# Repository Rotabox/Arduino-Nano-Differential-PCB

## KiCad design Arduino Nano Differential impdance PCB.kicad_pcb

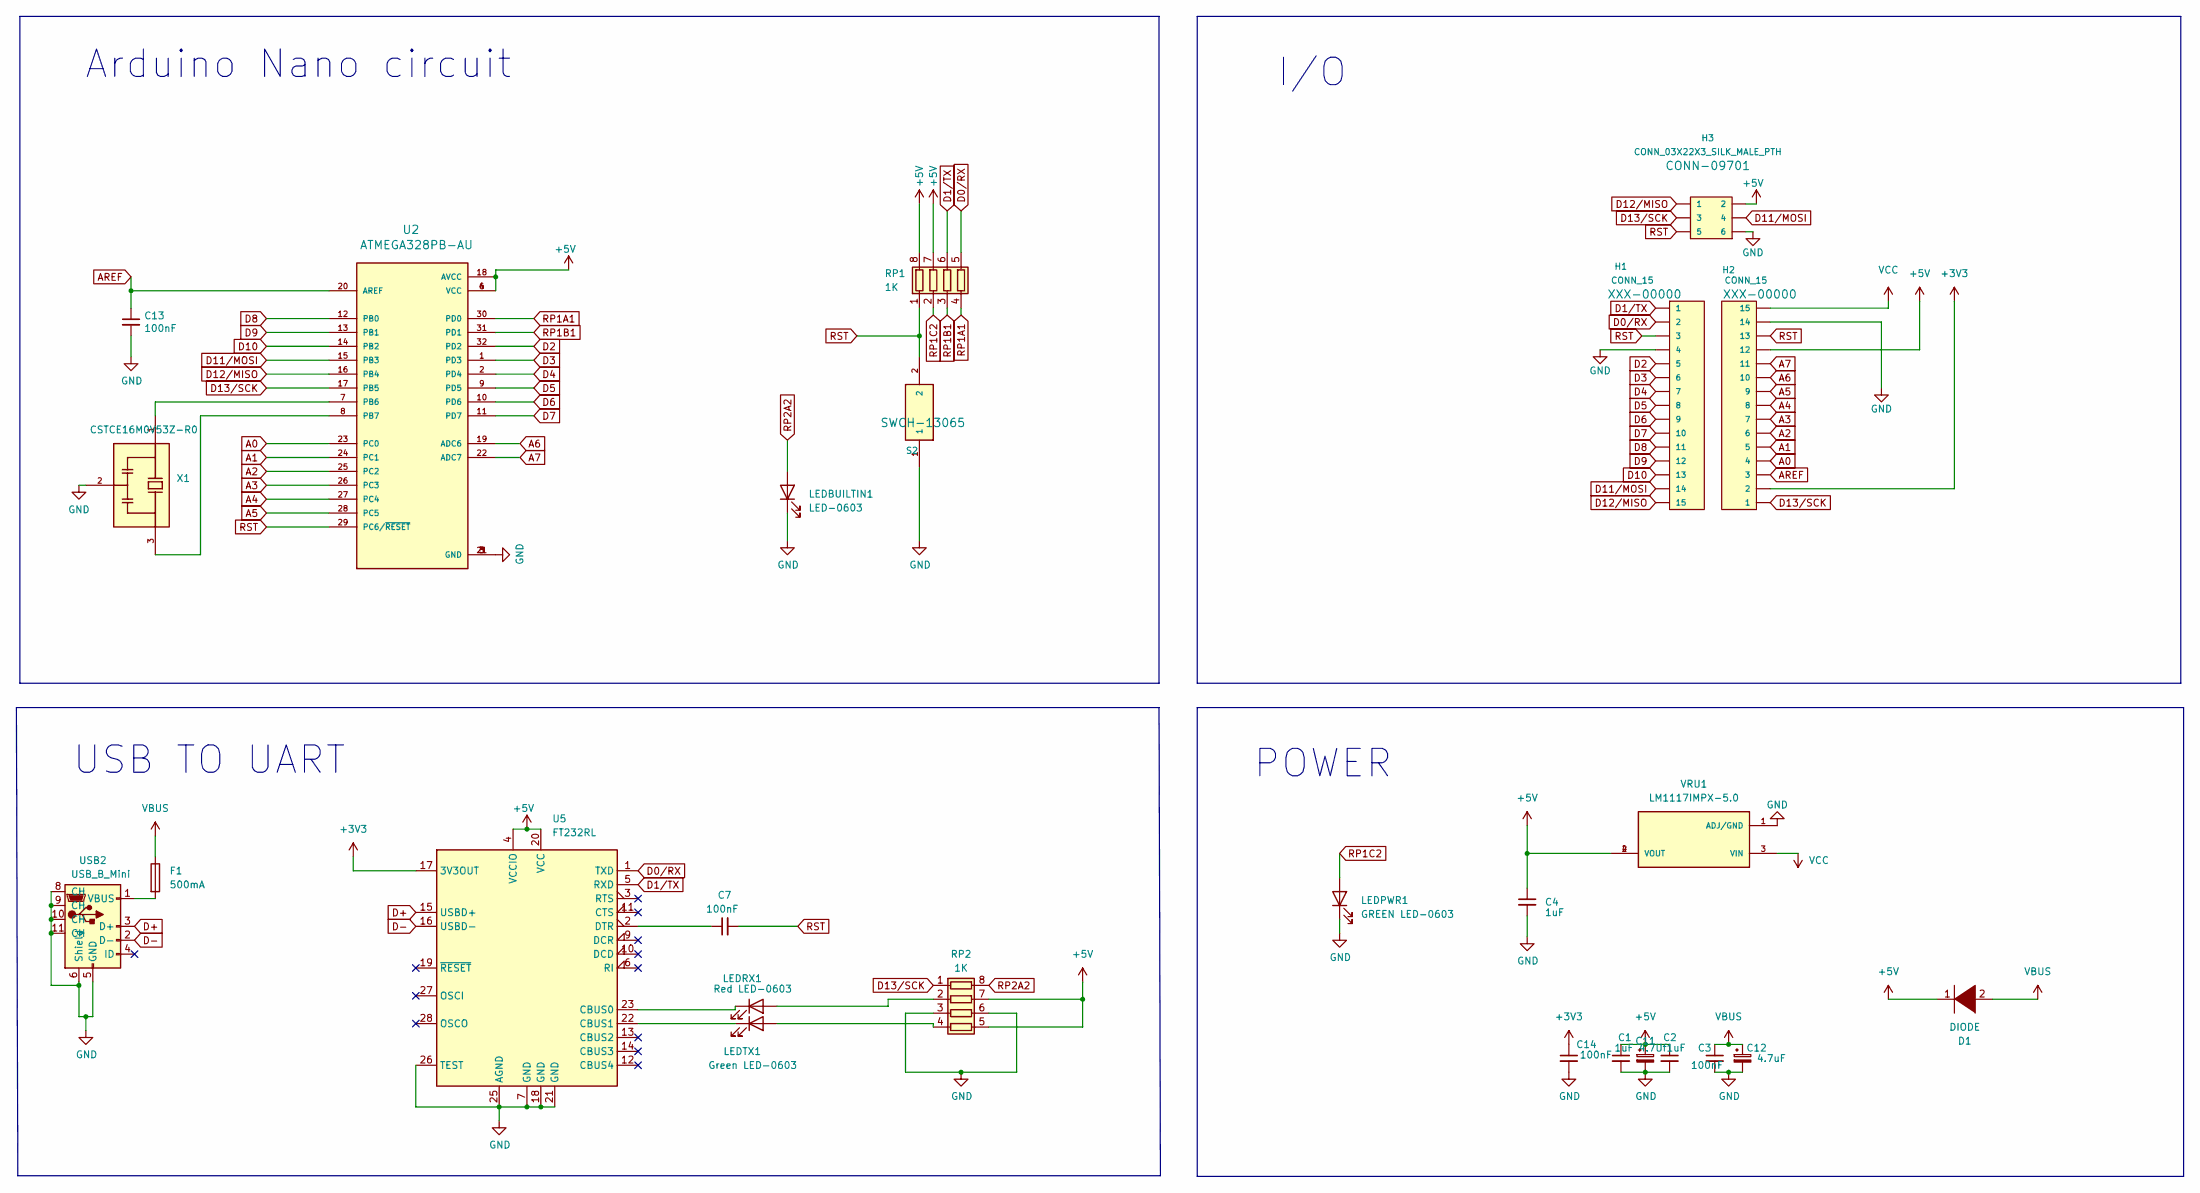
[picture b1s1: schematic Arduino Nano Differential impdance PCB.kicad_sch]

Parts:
C1, C2, C4: 1uF; C_0603_1608Metric
C3, C7, C13, C14: 100nF; C_0603_1608Metric
C11: 4.7Uf; C_1206_3216Metric_Pad1.33x1.80mm_HandSolder
C12: 4.7uF; C_1206_3216Metric_Pad1.33x1.80mm_HandSolder
D1: DIODE; DIO_SS3P3HM3_85A
F1: 500mA; Fuse_1812_4532Metric
H1, H2: CONN_15; PinHeader_1x15_P2.54mm_Vertical
H3: CONN_03X22X3_SILK_MALE_PTH; PinHeader_2x03_P2.54mm_Vertical
LEDBUILTIN1: LED-0603; LED_0603_1608Metric
LEDPWR1: GREEN LED-0603; LED_0603_1608Metric
LEDRX1: Red LED-0603; LED_0603_1608Metric
LEDTX1: Green LED-0603; LED_0603_1608Metric
RP1, RP2: 1K; R_Array_Convex_4x0603
S2: SW; SKRK; Manufacturer_Part_Number SKRKAEE010
U2: ATMEGA328PB-AU; QFP80P900X900X120-32N; MPN ATMEGA328PB-AU; Digi-Key_PN ATMEGA328PB-AU-ND
U5: FT232RL; SSOP-28_5.3x10.2mm_P0.65mm
USB2: USB_B_Mini; 67503-1020
VRU1: LM1117IMPX-5.0; SOT230P700X180-4N; PARTREV O
X1: CSTCE16M0V53Z-R0; OSC_CSTCE16M0V53Z-R0; PARTREV May 7, 2019

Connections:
+3V3: C14.1, H2.2, U5.17 (3V3OUT)
+5V: C1.1, C2.1, C4.1, C11.1, D1.1 (A), H2.12, H3.2, RP1.7 (R2.2), RP1.8 (R1.2), RP2.5 (R4.2), RP2.7 (R2.2), U2.4 (VCC), U2.6 (VCC), U2.18 (AVCC), U5.4 (VCCIO), U5.20 (VCC), VRU1.2 (VOUT), VRU1.4 (VOUT)
A0: H2.4, U2.23 (PC0)
A1: H2.5, U2.24 (PC1)
A2: H2.6, U2.25 (PC2)
A3: H2.7, U2.26 (PC3)
A4: H2.8, U2.27 (PC4)
A5: H2.9, U2.28 (PC5)
A6: H2.10, U2.19 (ADC6)
A7: H2.11, U2.22 (ADC7)
AREF: C13.1, H2.3, U2.20 (AREF)
D0/RX: H1.2, RP1.5 (R4.2), U5.1 (TXD)
D1/TX: H1.1, RP1.6 (R3.2), U5.5 (RXD)
D2: H1.5, U2.32 (PD2)
D3: H1.6, U2.1 (PD3)
D4: H1.7, U2.2 (PD4)
D5: H1.8, U2.9 (PD5)
D6: H1.9, U2.10 (PD6)
D7: H1.10, U2.11 (PD7)
D8: H1.11, U2.12 (PB0)
D9: H1.12, U2.13 (PB1)
D10: H1.13, U2.14 (PB2)
D11/MOSI: H1.14, H3.4, U2.15 (PB3)
D12/MISO: H1.15, H3.1, U2.16 (PB4)
D13/SCK: H2.1, H3.3, RP2.1 (R1.1), U2.17 (PB5)
D+: U5.15 (USBD+), USB2.3 (D+)
D-: U5.16 (USBD-), USB2.2 (D-)
GND: C1.2, C2.2, C3.2, C4.2, C11.2, C12.2, C13.2, C14.2, H1.4, H2.14, H3.6, LEDBUILTIN1.1 (K), LEDPWR1.1 (K), RP2.3 (R3.1), RP2.6 (R3.2), S2.1, U2.3 (GND), U2.5 (GND), U2.21 (GND), U5.7 (GND), U5.18 (GND), U5.21 (GND), U5.25 (AGND), U5.26 (TEST), USB2.5 (GND), USB2.6 (Shield), USB2.8 (CH), USB2.9 (CH), USB2.10 (CH), USB2.11 (CH), VRU1.1 (ADJ/GND), X1.2
unnamed: C7.1, U5.2 (DTR)
unnamed: F1.2, USB2.1 (VBUS)
unnamed: LEDRX1.1 (K), U5.23 (CBUS0)
unnamed: LEDRX1.2 (A), RP2.2 (R2.1)
unnamed: LEDTX1.1 (K), U5.22 (CBUS1)
unnamed: LEDTX1.2 (A), RP2.4 (R4.1)
unnamed: U2.7 (PB6), X1.1
unnamed: U2.8 (PB7), X1.3
RP1A1: RP1.4 (R4.1), U2.30 (PD0)
RP1B1: RP1.3 (R3.1), U2.31 (PD1)
RP1C2: LEDPWR1.2 (A), RP1.2 (R2.1)
RP2A2: LEDBUILTIN1.2 (A), RP2.8 (R1.2)
RST: C7.2, H1.3, H2.13, H3.5, RP1.1 (R1.1), S2.2, U2.29 (PC6/~RESET)
VBUS: C3.1, C12.1, D1.2 (K), F1.1
VCC: H2.15, VRU1.3 (VIN)

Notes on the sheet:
POWER
I/O
Arduino Nano circuit
USB TO UART

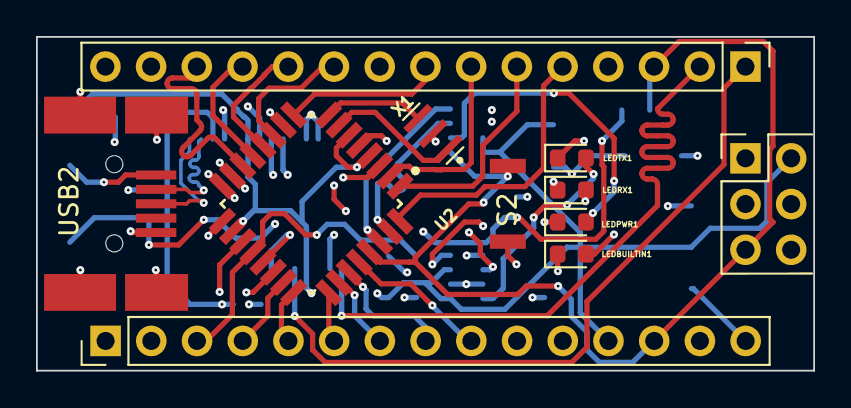
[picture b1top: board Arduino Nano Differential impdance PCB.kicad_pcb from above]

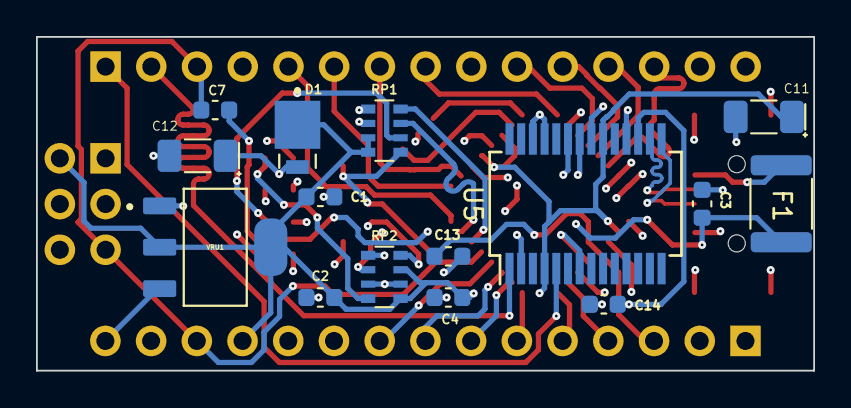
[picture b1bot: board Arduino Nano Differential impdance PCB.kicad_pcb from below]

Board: 4 copper layers, 43.2 x 18.5 mm, 26 parts (15 on the bottom side), 43 nets.
